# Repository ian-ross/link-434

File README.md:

# link-434

ISM 434 MHz band communications system:

 - Silicon Labs EFM8UB3 microcontroller.
 - Maxim MAX7032 434 MHz transceiver.
 - USB "dongle" form factor.
 - Flexible interface: USB or UART via 0.1" header.
 - C2 programming interface.

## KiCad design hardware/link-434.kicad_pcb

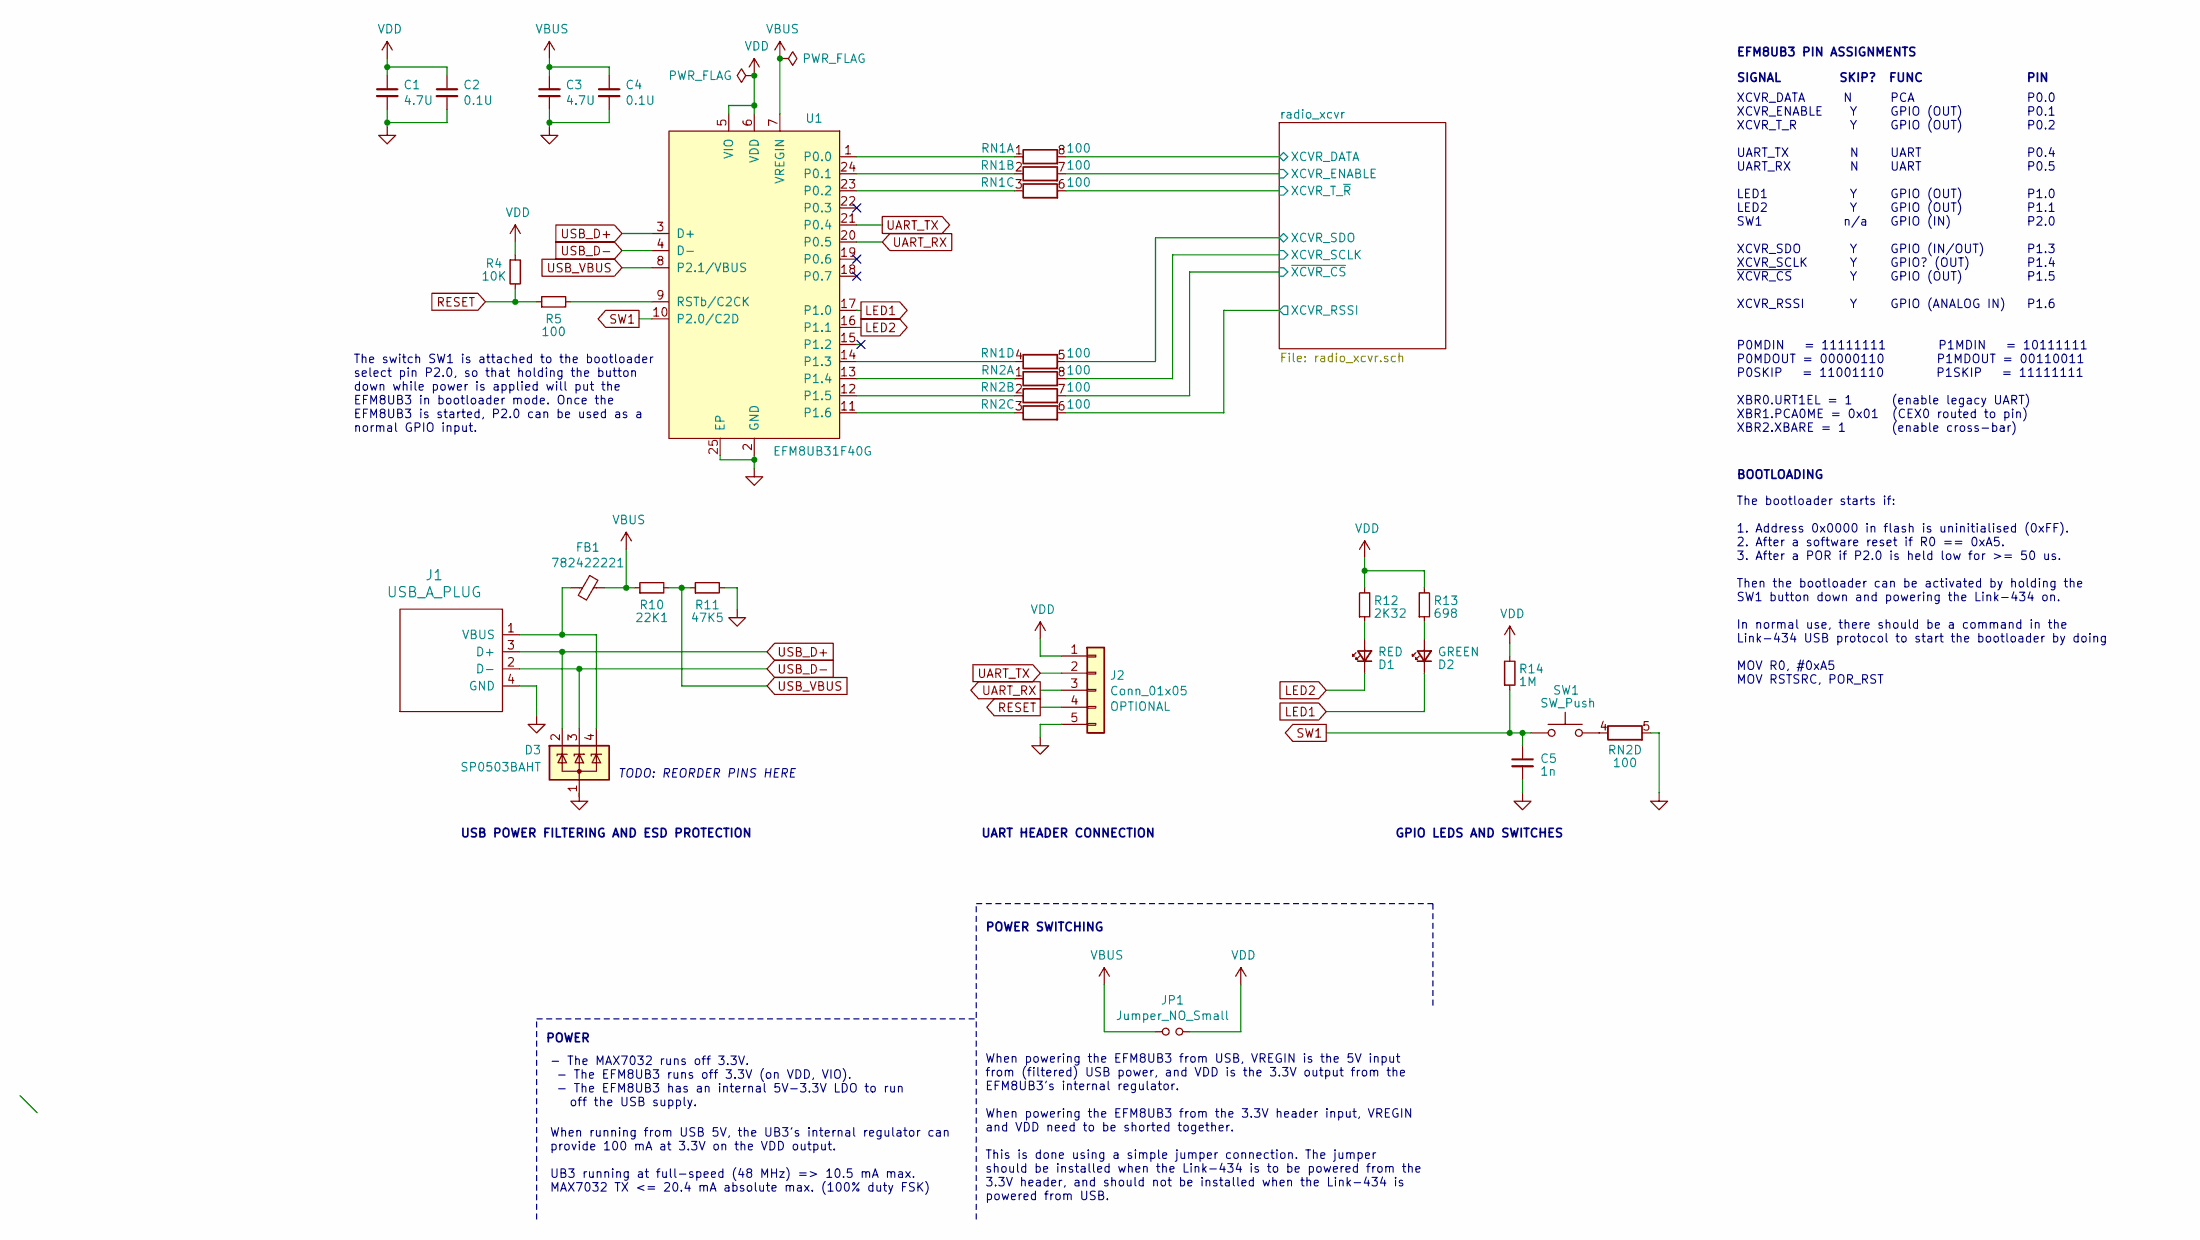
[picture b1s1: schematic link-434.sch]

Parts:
C1, C3: 4.7U; C_0402_1005Metric
C2, C4: 0.1U; C_0402_1005Metric
C5: 1n; C_0402_1005Metric
D1: RED; LED_0805_2012Metric
D2: GREEN; LED_0805_2012Metric
D3: SP0503BAHT; SOT-143; MPN SP0503BAHTG
FB1: 782422221; Ferrite_0402_1005Metric; MPN 782422221
J1: USB_A_PLUG; usb-a-edge
J2: Conn_01x05; PinHeader_1x05_P2.54mm_Vertical
JP1: Jumper_NO_Small; PinHeader_1x02_P2.54mm_Vertical
R4: 10K; R_0402_1005Metric
R5: 100; R_0402_1005Metric
R10: 22K1; R_0402_1005Metric
R11: 47K5; R_0402_1005Metric
R12: 2K32; R_0402_1005Metric
R13: 698; R_0402_1005Metric
R14: 1M; R_0402_1005Metric
RN1, RN2: 100; CAT16101J4LF
SW1: SW_Push; PTS526SM15SMTR2LFS; MPN PTS526 SM15 SMTR2 LFS
U1: EFM8UB31F40G; QFN-24-1EP_4x4mm_P0.5mm_EP2.6x2.6mm_ThermalVias; MPN EFM8UB31F40G-A-QFN24

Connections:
/radio_xcvr/XCVR_DATA: RN1.8 (R1.2); also elsewhere on the board
/radio_xcvr/XCVR_ENABLE: RN1.7 (R2.2); also elsewhere on the board
/radio_xcvr/XCVR_RSSI: RN2.6 (R3.2); also elsewhere on the board
/radio_xcvr/XCVR_SCLK: RN2.8 (R1.2); also elsewhere on the board
/radio_xcvr/XCVR_SDO: RN1.5 (R4.2); also elsewhere on the board
/radio_xcvr/XCVR_T_~R: RN1.6 (R3.2); also elsewhere on the board
/radio_xcvr/~XCVR_CS: RN2.7 (R2.2); also elsewhere on the board
GND: C1.2, C2.2, C3.2, C4.2, C5.2, D3.1 (A), J1.4 (GND), J2.5, R11.2, RN2.5 (R4.2), U1.2 (GND), U1.25 (EP); also elsewhere on the board
LED1: D2.1 (K), U1.17 (P1.0)
LED2: D1.1 (K), U1.16 (P1.1)
unnamed: D1.2 (A), R12.1
unnamed: D2.2 (A), R13.1
unnamed: D3.4 (K), FB1.2, J1.1 (VBUS)
unnamed: R5.2, U1.9 (RSTb/C2CK)
unnamed: RN1.1 (R1.1), U1.1 (P0.0)
unnamed: RN1.2 (R2.1), U1.24 (P0.1)
unnamed: RN1.3 (R3.1), U1.23 (P0.2)
unnamed: RN1.4 (R4.1), U1.14 (P1.3)
unnamed: RN2.1 (R1.1), U1.13 (P1.4)
unnamed: RN2.2 (R2.1), U1.12 (P1.5)
unnamed: RN2.3 (R3.1), U1.11 (P1.6)
unnamed: RN2.4 (R4.1), SW1.2
RESET: J2.4, R4.2, R5.1
SW1: C5.1, R14.1, SW1.1, U1.10 (P2.0/C2D)
UART_RX: J2.3, U1.20 (P0.5)
UART_TX: J2.2, U1.21 (P0.4)
USB_D+: D3.2 (K), J1.3 (D+), U1.3 (D+)
USB_D-: D3.3 (K), J1.2 (D-), U1.4 (D-)
USB_VBUS: R10.2, R11.1, U1.8 (P2.1/VBUS)
VBUS: C3.1, C4.1, FB1.1, JP1.1, R10.1, U1.7 (VREGIN)
VDD: C1.1, C2.1, J2.1, JP1.2, R4.1, R12.2, R13.2, R14.2, U1.5 (VIO), U1.6 (VDD); also elsewhere on the board

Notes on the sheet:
BOOTLOADING
When powering the EFM8UB3 from USB, VREGIN is the 5V input from (filtered) USB power, and VDD is the 3.3V output from the EFM8UB3's internal regulator. When powering the EFM8UB3 from the 3.3V header input, VREGIN and VDD need to be shorted together. This is done using a simple jumper connection. Th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
POWER SWITCHING
When running from USB 5V, the UB3's internal regulator can provide 100 mA at 3.3V on the VDD output. UB3 running at full-speed (48 MHz) => 10.5 mA max. MAX7032 TX <= 20.4 mA absolute max. (100% duty FSK)
POWER
- The MAX7032 runs off 3.3V. - The EFM8UB3 runs off 3.3V (on VDD, VIO). - The EFM8UB3 has an internal 5V-3.3V LDO to run off the USB supply.
USB POWER FILTERING AND ESD PROTECTION
GPIO LEDS AND SWITCHES
UART HEADER CONNECTION
EFM8UB3 PIN ASSIGNMENTS
XCVR_DATA XCVR_ENABLE XCVR_T_R UART_TX UART_RX LED1 LED2 SW1 XCVR_SDO XCVR_SCLK ~XCVR_CS~ XCVR_RSSI
N Y Y N N Y Y n/a Y Y Y Y
PCA GPIO (OUT) GPIO (OUT) UART UART GPIO (OUT) GPIO (OUT) GPIO (IN) GPIO (IN/OUT) GPIO? (OUT) GPIO (OUT) GPIO (ANALOG IN)
P0.0 P0.1 P0.2 P0.4 P0.5 P1.0 P1.1 P2.0 P1.3 P1.4 P1.5 P1.6
P0MDIN = 11111111 P1MDIN = 10111111 P0MDOUT = 00000110 P1MDOUT = 00110011 P0SKIP = 11001110 P1SKIP = 11111111 XBR0.URT1EL = 1 (enable legacy UART) XBR1.PCA0ME = 0x01 (CEX0 routed to pin) XBR2.XBARE = 1 (enable cross-bar)
SIGNAL SKIP? FUNC PIN
The bootloader starts if: 1. Address 0x0000 in flash is uninitialised (0xFF). 2. After a software reset if R0 == 0xA5. 3. After a POR if P2.0 is held low for >= 50 us. Then the bootloader can be activated by holding the SW1 button down and powering the Link-434 on. In normal use, there should be a 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
The switch SW1 is attached to the bootloader select pin P2.0, so that holding the button down while power is applied will put the EFM8UB3 in bootloader mode. Once the EFM8UB3 is started, P2.0 can be used as a normal GPIO input.
TODO: REORDER PINS HERE

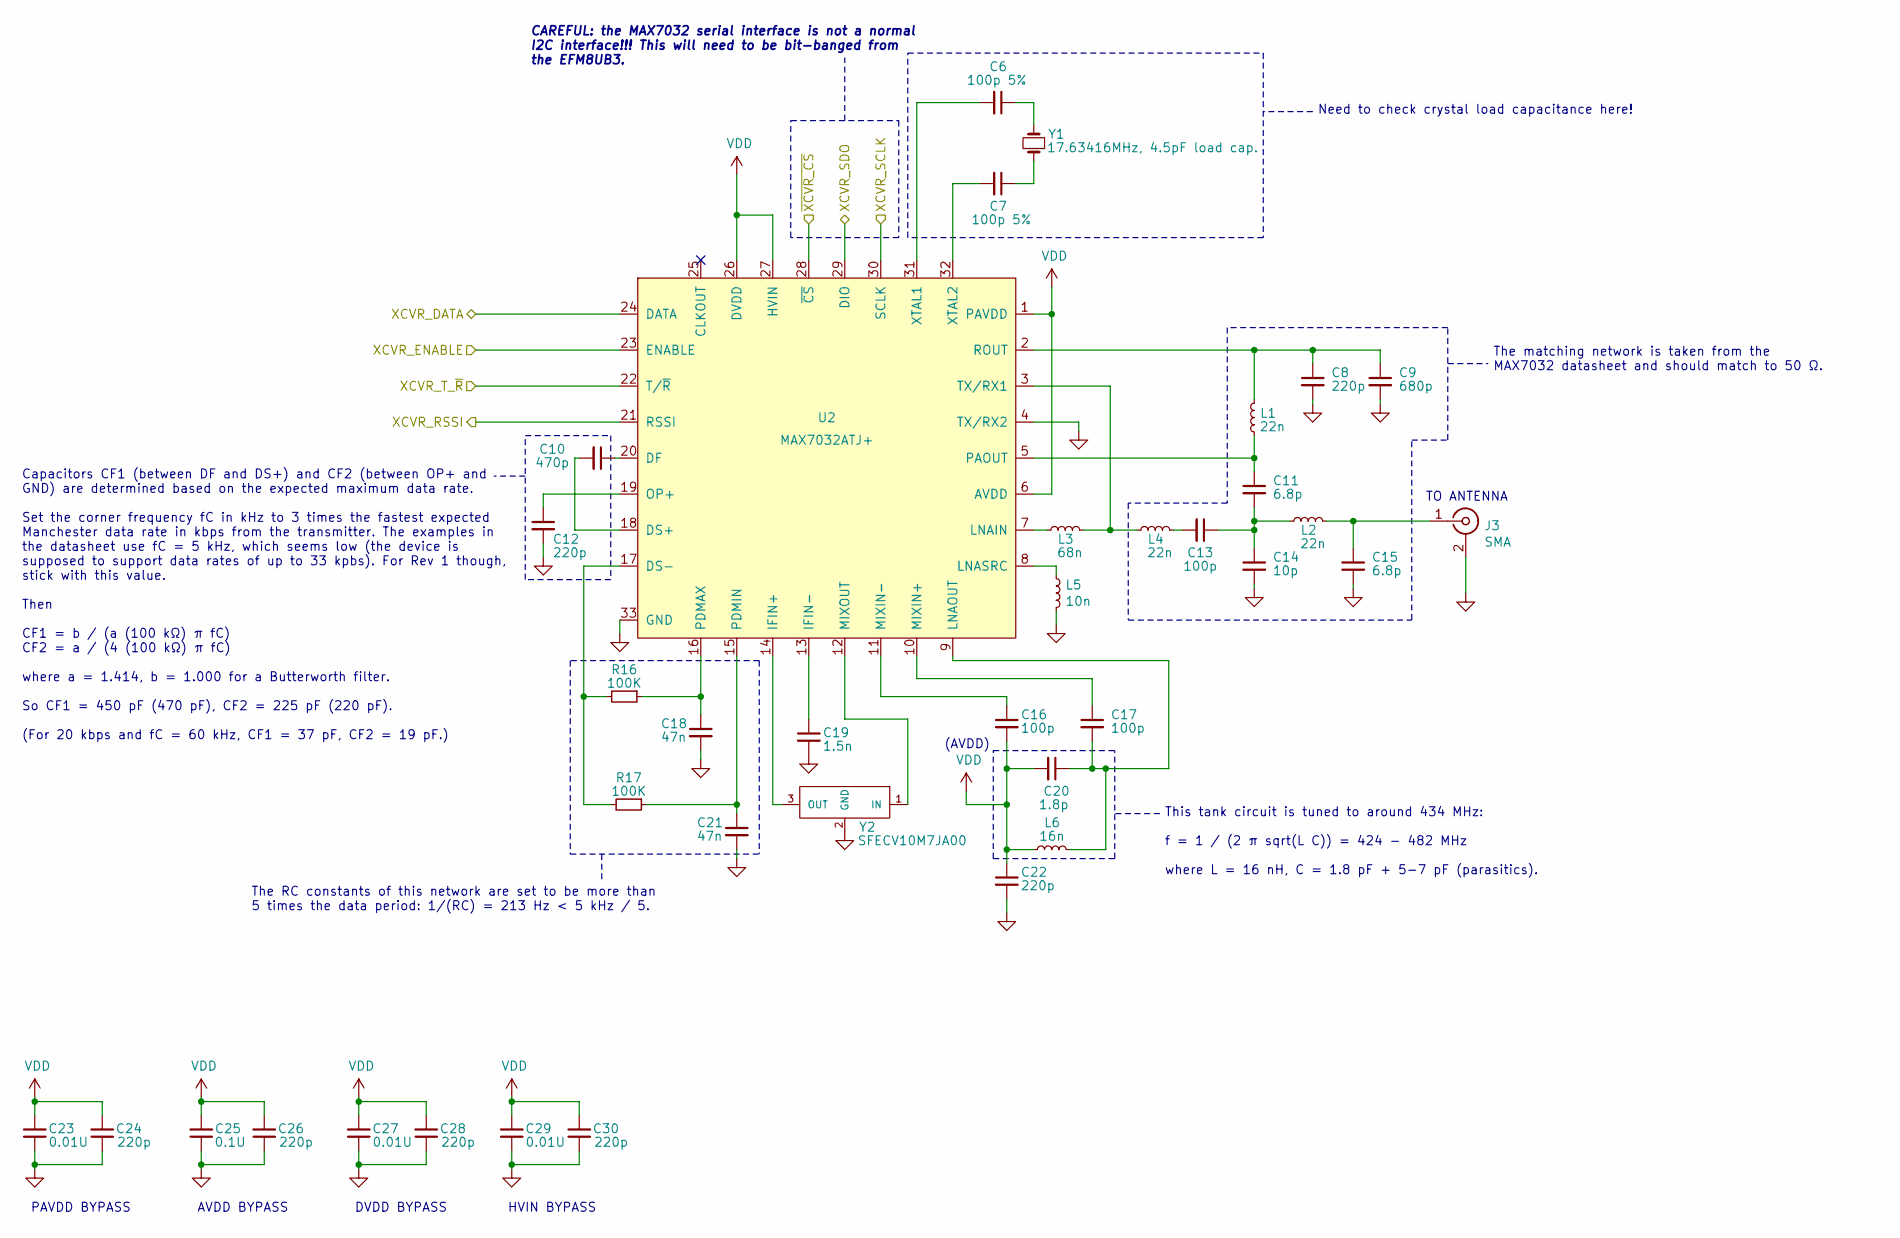
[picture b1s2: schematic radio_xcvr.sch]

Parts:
C6, C7: 100p 5%; C_0402_1005Metric
C8, C12, C22, C24, C26, C28, C30: 220p; C_0402_1005Metric
C9: 680p; C_0402_1005Metric
C10: 470p; C_0402_1005Metric
C11, C15: 6.8p; C_0402_1005Metric
C13, C16, C17: 100p; C_0402_1005Metric
C14: 10p; C_0402_1005Metric
C18, C21: 47n; C_0402_1005Metric
C19: 1.5n; C_0402_1005Metric
C20: 1.8p; C_0402_1005Metric
C23, C27, C29: 0.01U; C_0402_1005Metric
C25: 0.1U; C_0402_1005Metric
J3: SMA; SMA_Linx_CONSMA001_Vertical; MPN CONSMA001-C-G
L1, L2, L4: 22n; L_Coilcraft_0603CS; MPN 0603CS-22NXJLW
L3: 68n; L_Coilcraft_0603CS; MPN 0603CS-68NXJLW
L5: 10n; L_Coilcraft_0603CS; MPN 0603CS-10NXJLU
L6: 16n; L_Murata_LQW18ASxxxx00x; MPN LQW18AS16NJ00D
R16, R17: 100K; R_0402_1005Metric
U2: MAX7032ATJ+; QFN-32-1EP_5x5mm_P0.5mm_EP3.1x3.1mm_ThermalVias; MPN MAX7032ATJ+
Y1: 17.63416MHz, 4.5pF load cap.; Crystal_SMD_HC49-SD; MPN 017301
Y2: SFECV10M7JA00; Resonator_SMD_muRata_SFECV-3Pin_6.9x2.9mm; MPN SFECV10M7JA00-R0

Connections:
/radio_xcvr/XCVR_DATA: U2.24 (DATA); also elsewhere on the board
/radio_xcvr/XCVR_ENABLE: U2.23 (ENABLE); also elsewhere on the board
/radio_xcvr/XCVR_RSSI: U2.21 (RSSI); also elsewhere on the board
/radio_xcvr/XCVR_SCLK: U2.30 (SCLK); also elsewhere on the board
/radio_xcvr/XCVR_SDO: U2.29 (DIO); also elsewhere on the board
/radio_xcvr/XCVR_T_~R: U2.22 (T/~R); also elsewhere on the board
/radio_xcvr/~XCVR_CS: U2.28 (~CS); also elsewhere on the board
GND: C8.2, C9.2, C12.2, C14.2, C15.2, C18.2, C19.2, C21.2, C22.2, C23.1, C24.1, C25.1, C26.1, C27.1, C28.1, C29.1, C30.1, J3.2 (Ext), L5.2, U2.4 (TX/RX2), U2.33 (GND), Y2.2 (GND); also elsewhere on the board
unnamed: C6.1, Y1.2
unnamed: C6.2, U2.31 (XTAL1)
unnamed: C7.1, Y1.1
unnamed: C7.2, U2.32 (XTAL2)
unnamed: C8.1, C9.1, L1.2, U2.2 (ROUT)
unnamed: C10.1, U2.20 (DF)
unnamed: C10.2, U2.18 (DS+)
unnamed: C11.1, L1.1, U2.5 (PAOUT)
unnamed: C11.2, C13.1, C14.1, L2.1
unnamed: C12.1, U2.19 (OP+)
unnamed: C13.2, L4.2
unnamed: C15.1, J3.1 (In), L2.2
unnamed: C16.1, U2.11 (MIXIN-)
unnamed: C17.1, U2.10 (MIXIN+)
unnamed: C17.2, C20.1, L6.2, U2.9 (LNAOUT)
unnamed: C18.1, R16.1, U2.16 (PDMAX)
unnamed: C19.1, U2.13 (IFIN-)
unnamed: C21.1, R17.1, U2.15 (PDMIN)
unnamed: L3.1, U2.7 (LNAIN)
unnamed: L3.2, L4.1, U2.3 (TX/RX1)
unnamed: L5.1, U2.8 (LNASRC)
unnamed: R16.2, R17.2, U2.17 (DS-)
unnamed: U2.12 (MIXOUT), Y2.1 (IN)
unnamed: U2.14 (IFIN+), Y2.3 (OUT)
VDD: C16.2, C20.2, C22.1, C23.2, C24.2, C25.2, C26.2, C27.2, C28.2, C29.2, C30.2, L6.1, U2.1 (PAVDD), U2.6 (AVDD), U2.26 (DVDD), U2.27 (HVIN); also elsewhere on the board

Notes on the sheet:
TO ANTENNA
PAVDD BYPASS
AVDD BYPASS
(AVDD)
DVDD BYPASS
HVIN BYPASS
Capacitors CF1 (between DF and DS+) and CF2 (between OP+ and GND) are determined based on the expected maximum data rate. Set the corner frequency fC in kHz to 3 times the fastest expected Manchester data rate in kbps from the transmitter. The examples in the datasheet use fC = 5 kHz, which seems l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
The RC constants of this network are set to be more than 5 times the data period: 1/(RC) = 213 Hz < 5 kHz / 5.
This tank circuit is tuned to around 434 MHz: f = 1 / (2 π sqrt(L C)) = 424 - 482 MHz where L = 16 nH, C = 1.8 pF + 5-7 pF (parasitics).
The matching network is taken from the MAX7032 datasheet and should match to 50 Ω.
CAREFUL: the MAX7032 serial interface is not a normal I2C interface!!! This will need to be bit-banged from the EFM8UB3.
Need to check crystal load capacitance here!

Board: 2 copper layers, 60 parts (0 on the bottom side), 55 nets, no tracks yet.

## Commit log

2020-09-26 Initial schematic capture
2020-10-14 Thunderboard assembly blinky
2020-10-20 Schematic reorganisation
2020-10-21 Schematic checklist
2020-10-27 Tidying
2020-11-21 Reorganised Thunderboard blinky experiments
